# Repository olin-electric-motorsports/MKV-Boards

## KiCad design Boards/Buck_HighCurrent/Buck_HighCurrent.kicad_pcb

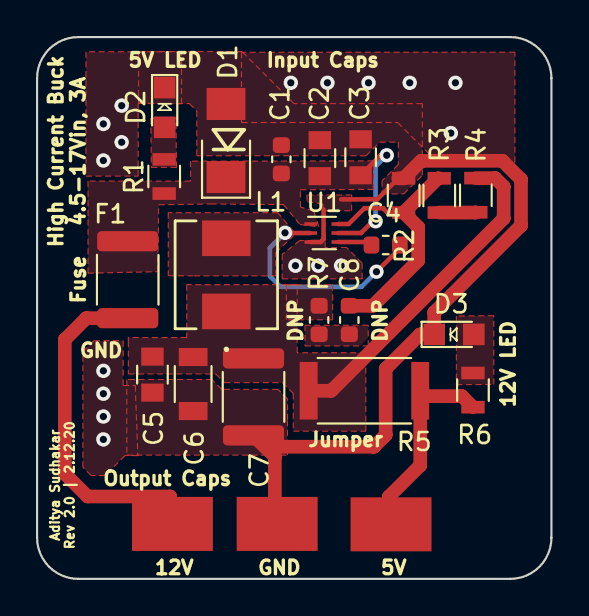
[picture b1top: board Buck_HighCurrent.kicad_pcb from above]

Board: 2 copper layers, 28.6 x 30.1 mm, 24 parts (0 on the bottom side), 12 nets.

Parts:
C1: C_0.1uF; C_0603_1608Metric
C2, C3: C_10uF_25V; C_0805_OEM
C4: C_0.1uF_0603; C_0603_1608Metric
C5: C_10uF; C_0805_OEM
C6: C_22uF; C_1206_OEM
C7: C_33uF; C_1812_4532Metric
C8: C_100nF_DNP; C_0603_1608Metric
D1: D_Zener_18V; DO-214AA
D2, D3: LED_0805; LED_0805_OEM
F1: F_2.6A_16V; Fuse_1812_4532Metric
L1: L_4.7uH_3.2A; IHLP2020BZER4R7M11
R1: R_1K; R_0805_OEM
R2: R_10K; R_0805_OEM
R3: R_51.1K; R_0805_OEM
R4: R_22K; R_0805_OEM
R5: R_0_2512; R_2512_OEM
R6: R_200; R_0805_OEM
R7: R_1_DNP; R_0603_1608Metric
TP1, TP2, TP3: Test_Point_SMD
U1: TPS563231; SOT-563

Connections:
/12V: F1.2, TP1.1
GND: C1.2, C2.2, C3.2, C5.2, C6.2, C7.2, D1.2, D2.1, D3.1, R2.2, TP3.1, U1.3
unnamed: C1.1, C2.1, C3.1, D1.1, F1.1, R1.1, U1.1, U1.5
unnamed: C4.1, L1.2, U1.2
unnamed: C4.2, U1.4
unnamed: C5.1, C6.1, C7.1, L1.1, R4.1, R5.2, R7.2
unnamed: C8.1, R2.1, R3.2, U1.6
unnamed: C8.2, R7.1
unnamed: D2.2, R1.2
unnamed: D3.2, R6.2
unnamed: R3.1, R4.2
VCC: R5.1, R6.1, TP2.1

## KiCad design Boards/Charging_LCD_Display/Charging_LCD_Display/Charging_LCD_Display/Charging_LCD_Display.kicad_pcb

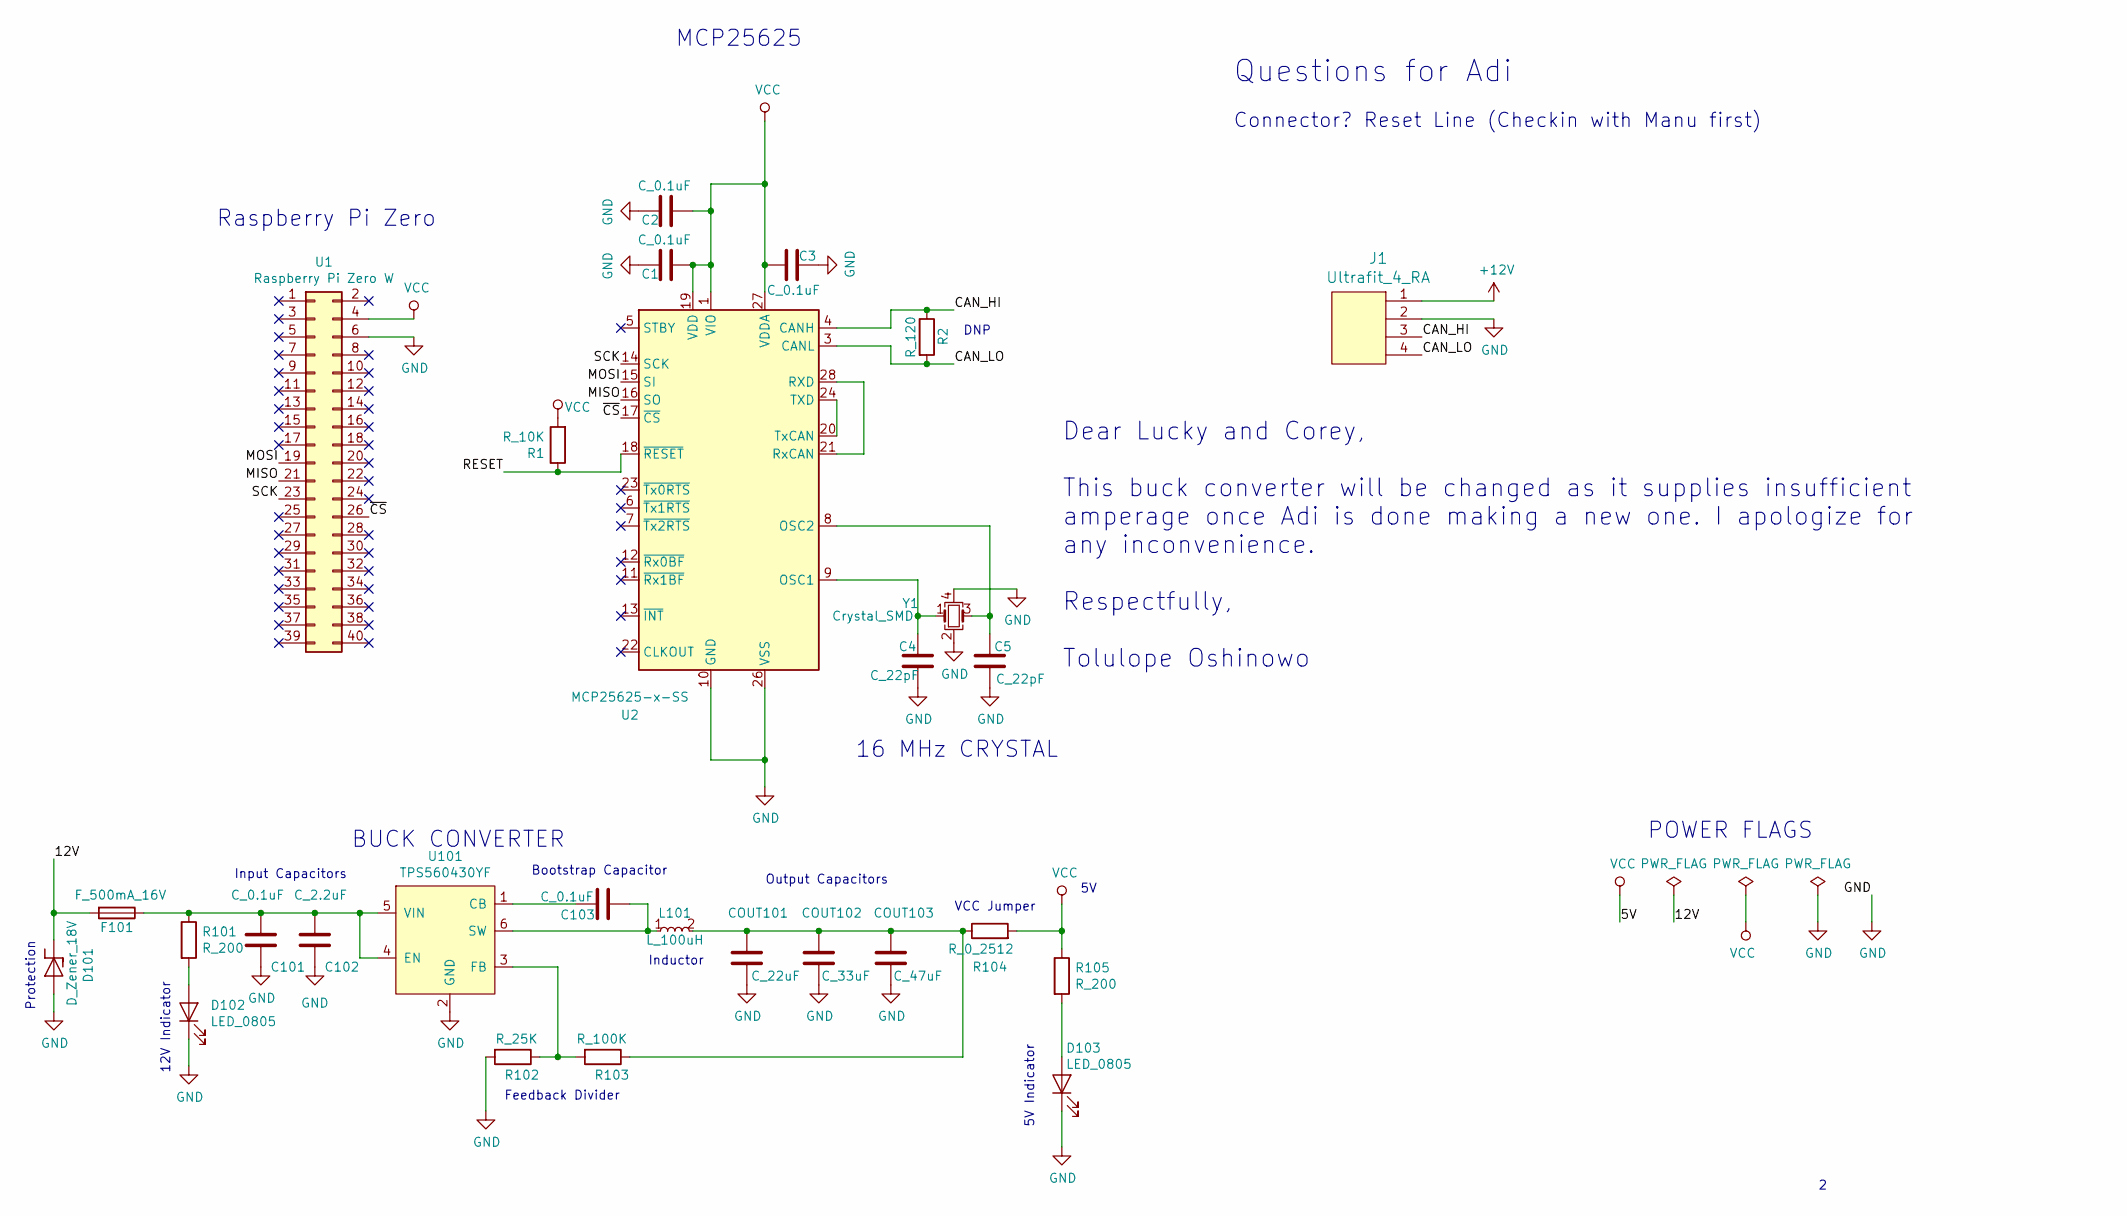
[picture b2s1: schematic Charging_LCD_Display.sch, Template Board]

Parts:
C1, C2, C3, C101, C103: C_0.1uF; C_0805_OEM; MPN 478-3352-1-ND
C4, C5: C_22pF; C_0805_OEM; MPN 1276-1130-1-ND
C102: C_2.2uF; C_0603_1608Metric; MPN 311-1451-1-ND
COUT101: C_22uF; C_1206_OEM; MPN 445-11693-1-ND
COUT102: C_33uF; Fuse_1812; MPN 445-3924-1-ND
COUT103: C_47uF; C_0805_OEM; MPN 1276-6467-1-ND
D101: D_Zener_18V; DO-214AA; MPN SMBJ5355B-TPMSCT-ND
D102, D103: LED_0805; LED_0805_OEM; MPN 475-1410-1-ND
F101: F_500mA_16V; Fuse_1210; MPN 507-1786-1-ND
J1: Ultrafit_4_RA; MPN WM11574-ND
L101: L_100uH; MPN 445-15759-1-ND
R1: R_10K; R_0805_OEM; MPN CRS0805-FX-1002ELFCT-ND
R2: R_120; R_0805_OEM; MPN RMCF0805JT200RCT-ND
R101, R105: R_200; R_0805_OEM; MPN RMCF0805JT200RCT-ND
R102: R_25K; R_0805_OEM; Digi-key Part Number CPF-A-0805B25KE
R103: R_100K; R_0805_OEM; MPN P100KCCT-ND
R104: R_0_2512; R_2512_OEM; MPN A121322CT-ND
U1: Raspberry Pi Zero W
U2: MCP25625-x-SS; SSOP-28_5.3x10.2mm_P0.65mm; MPN MCP25625-E/SS-ND
U101: TPS560430YF; SOT-23-6_OEM; MPN TPS560430YFDBVR
Y1: Crystal_SMD; Crystal_SMD_FA238; MPN 887-1125-1-ND

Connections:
+12V: J1.1
/12V: D101.1 (K), F101.2
/CAN_HI: J1.3, R2.1, U2.4 (CANH)
/CAN_LO: J1.4, R2.2, U2.3 (CANL)
/MISO: U1.21, U2.16 (SO)
/MOSI: U1.19, U2.15 (SI)
/RESET: R1.1, U2.18 (~RESET)
/SCK: U1.23, U2.14 (SCK)
/~CS: U1.26, U2.17 (~CS)
GND: C1.2, C2.2, C3.2, C4.2, C5.2, C101.2, C102.2, COUT101.2, COUT102.2, COUT103.2, D101.2 (A), D102.1 (K), D103.1 (K), J1.2, R102.2, U1.6, U2.10 (GND), U2.26 (VSS), U101.2 (GND), Y1.2, Y1.4
unnamed: C4.1, U2.9 (OSC1), Y1.1
unnamed: C5.1, U2.8 (OSC2), Y1.3
unnamed: C101.1, C102.1, F101.1, R101.1, U101.4 (EN), U101.5 (VIN)
unnamed: C103.1, U101.1 (CB)
unnamed: C103.2, L101.1, U101.6 (SW)
unnamed: COUT101.1, COUT102.1, COUT103.1, L101.2, R103.1, R104.1
unnamed: D102.2 (A), R101.2
unnamed: D103.2 (A), R105.2
unnamed: R102.1, R103.2, U101.3 (FB)
unnamed: U2.20 (TxCAN), U2.24 (TXD)
unnamed: U2.21 (RxCAN), U2.28 (RXD)
VCC: C1.1, C2.1, C3.1, R1.2, R104.2, R105.1, U1.4, U2.1 (VIO), U2.19 (VDD), U2.27 (VDDA)

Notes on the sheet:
12V Indicator
Protection
Feedback Divider
Inductor
Bootstrap Capacitor
Output Capacitors
VCC Jumper
5V Indicator
POWER FLAGS
16 MHz CRYSTAL
BUCK CONVERTER
Input Capacitors
DNP
MCP25625
Raspberry Pi Zero
Questions for Adi
Connector? Reset Line (Checkin with Manu first)
Dear Lucky and Corey, This buck converter will be changed as it supplies insufficient amperage once Adi is done making a new one. I apologize for any inconvenience. Respectfully, Tolulope Oshinowo

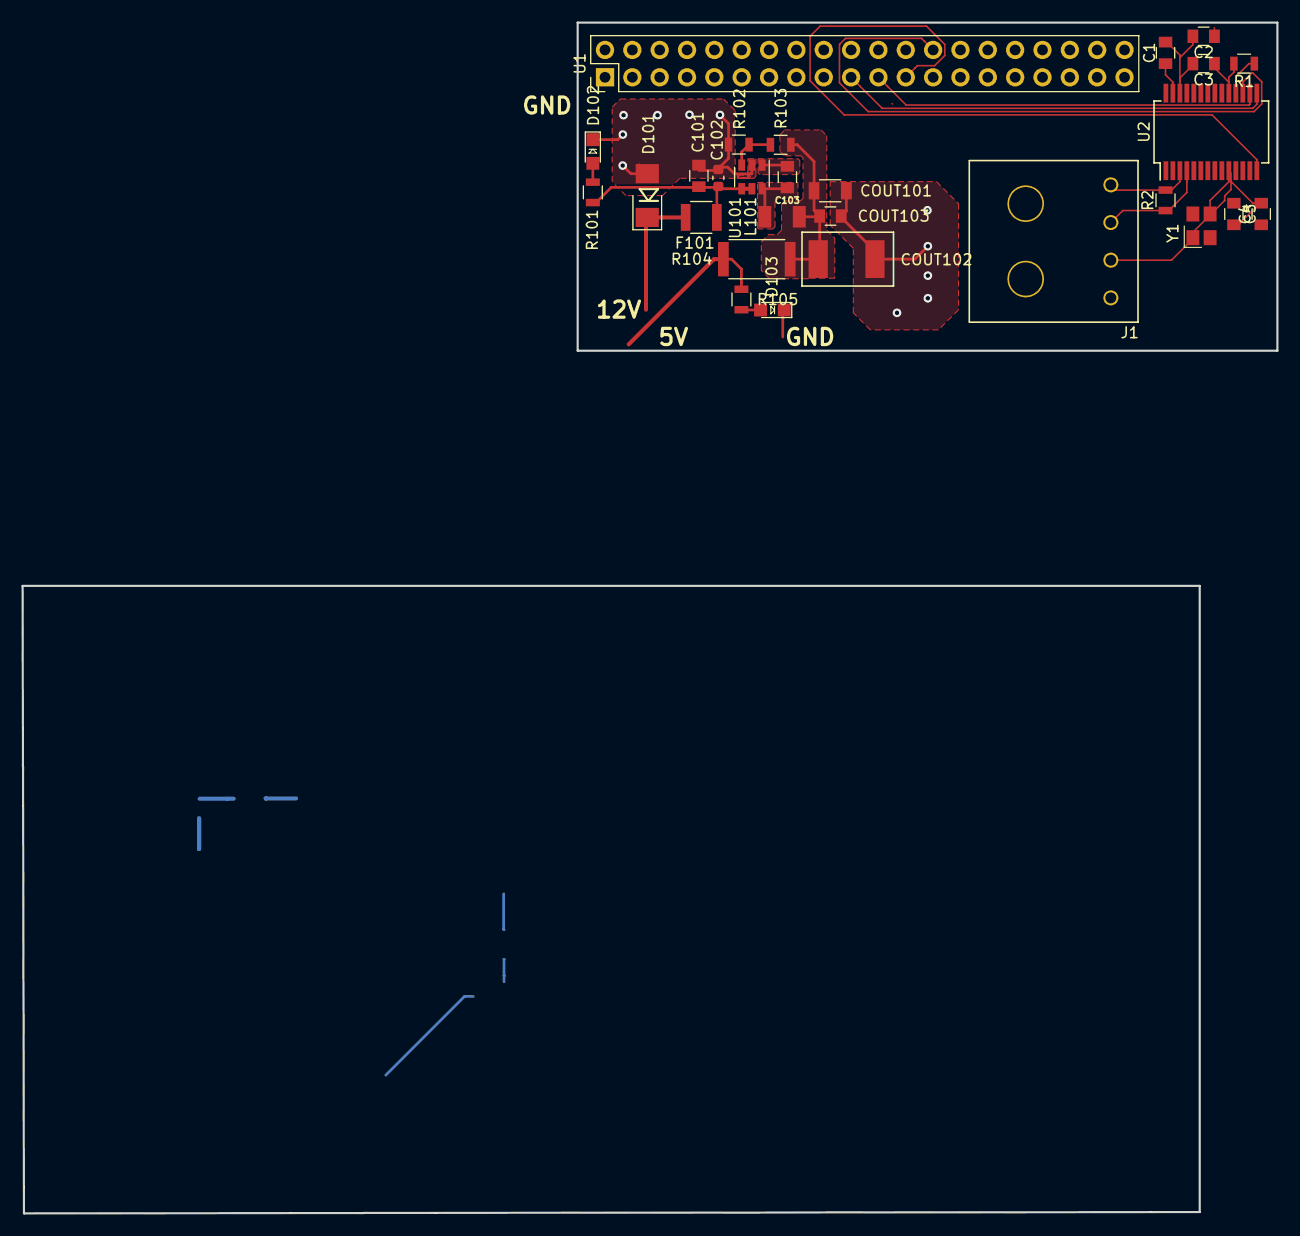
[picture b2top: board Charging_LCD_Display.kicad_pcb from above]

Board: 2 copper layers, 65.0 x 30.5 mm, 28 parts (0 on the bottom side), 21 nets.

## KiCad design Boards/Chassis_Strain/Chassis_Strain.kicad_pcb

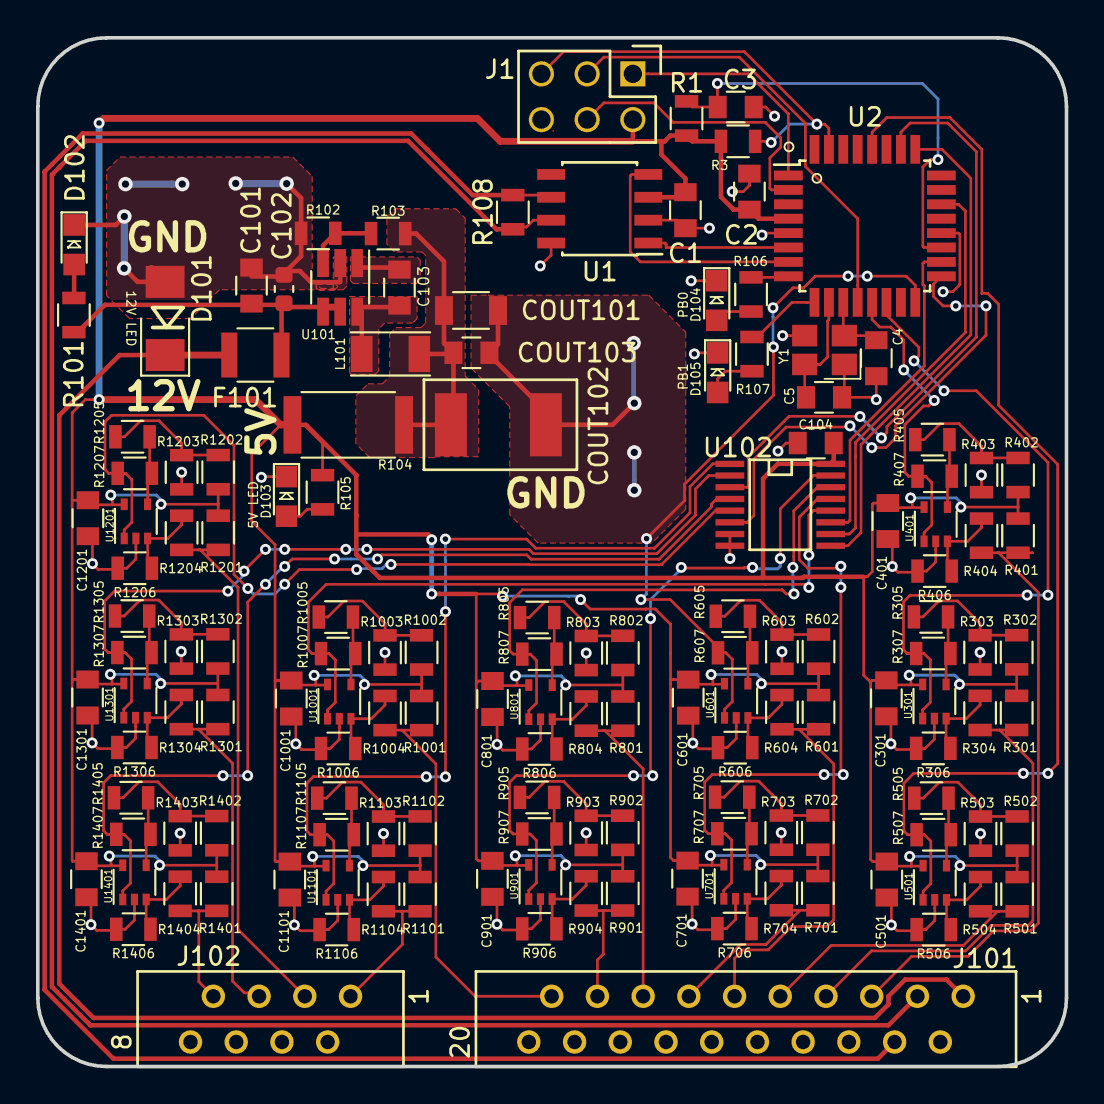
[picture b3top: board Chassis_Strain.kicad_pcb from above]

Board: 2 copper layers, 57.2 x 57.2 mm, 145 parts (0 on the bottom side), 90 nets.

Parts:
C1, C2, C101, C103, C104, C301, C401, C501, C601, C701, C801, C901, C1001, C1101, C1201, C1301, C1401: C_0.1uF; C_0805_OEM
C3: C_100pF; C_0805_OEM
C4, C5: C_30pF; C_0805_OEM
C102: C_2.2uF; C_0603_1608Metric
COUT101: C_22uF; C_1206_OEM
COUT102: C_33uF; Fuse_1812
COUT103: C_47uF; C_0805_OEM
D101: D_Zener_18V; DO-214AA
D102, D103, D104, D105: LED_0805; LED_0805_OEM
F101: F_500mA_16V; Fuse_1210
J1: CONN_02X03; Pin_Header_Straight_2x03
J101: MM_F_RA_20; micromatch_female_ra_20
J102: MM_F_RA_08; micromatch_female_ra_8
L101: L_100uH; L_100uH_OEM
R1: R_100; R_0805_OEM
R3: R_10K; R_0805_OEM
R101: R_1K; R_0805_OEM
R102: R_25K; R_0805_OEM
R103: R_100K; R_0805_OEM
R104: R_0_2512; R_2512_OEM
R105, R106, R107: R_200; R_0805_OEM
R108: R_120_DNP; R_0805_OEM
R301, R302, R303, R304, R305, R401, R402, R403, R404, R405, R501, R502, R503, R504, R505, R601, R602, R603, R604, R605, R701, R702, R703, R704, R705, R801, R802, R803, R804, R805, R901, R902, R903, R904, R905, R1001, R1002, R1003, R1004, R1005, R1101, R1102, R1103, R1104, R1105, R1201, R1202, R1203, R1204, R1205, R1301, R1302, R1303, R1304, R1305, R1401, R1402, R1403, R1404, R1405: R_120; R_0805_OEM
R306, R307, R406, R407, R506, R507, R606, R607, R706, R707, R806, R807, R906, R907, R1006, R1007, R1106, R1107, R1206, R1207, R1306, R1307, R1406, R1407: R_4.99K; R_0805_OEM
U1: MCP2561-E_SN; SOIC-8_3.9x4.9mm_Pitch1.27mm_OEM
U2: ATMEGA16M1; TQFP-32_7x7mm_Pitch0.8mm
U101: TPS560430YF; SOT-23-6_Handsoldering
U102: 74HC4051; TSSOP-16-OEM
U301, U401, U501, U601, U701, U801, U901, U1001, U1101, U1201, U1301, U1401: MCP6001T-I-LT; SOT-353_SC-70-5
Y1: Crystal_SMD; Crystal_SMD_FA238

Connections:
/12V: D101.1, F101.2, J101.1
/CAN_+: J101.3, R108.1, U1.7
/CAN_-: J101.4, R108.2, U1.6
/CAN_RX: U1.4, U2.7
/CAN_TX: U1.1, U2.6
/MISO: J1.1, U2.1
/MOSI: J1.4, U2.2
/RESET: J1.5, R3.2, U2.31
/SCK: J1.3, U2.12
/mux_enable_input: U2.17, U102.6
/mux_out_to_atmega_adc_6: U2.26, U102.3
/mux_select_S0: U2.18, U102.11
/mux_select_S1: U2.22, U102.10
/mux_select_S2: U2.25, U102.9
/sg_to_atmega_adc_2: R407.1, U2.13, U401.1
/sg_to_atmega_adc_3: R307.1, U2.14, U301.1
/sg_to_atmega_adc_4: R507.1, U2.28, U501.1
/sg_to_atmega_adc_5: R607.1, U2.16, U601.1
/sg_to_mux_Y0: R707.1, U102.13, U701.1
/sg_to_mux_Y1: R807.1, U102.14, U801.1
/sg_to_mux_Y2: R907.1, U102.15, U901.1
/sg_to_mux_Y3: R1007.1, U102.12, U1001.1
/sg_to_mux_Y4: R1107.1, U102.1, U1101.1
/sg_to_mux_Y5: R1207.1, U102.5, U1201.1
/sg_to_mux_Y6: R1307.1, U102.2, U1301.1
/sg_to_mux_Y7: R1407.1, U102.4, U1401.1
/strain_gauge_cluster/r_strain_1_+: J101.5, R401.1, R404.2
/strain_gauge_cluster/r_strain_2_+: J101.7, R301.1, R304.2
/strain_gauge_cluster/r_strain_3_+: J101.9, R501.1, R504.2
/strain_gauge_cluster/r_strain_4_+: J101.11, R601.1, R604.2
/strain_gauge_cluster/r_strain_5_+: J101.13, R701.1, R704.2
/strain_gauge_cluster/r_strain_6_+: J101.15, R801.1, R804.2
/strain_gauge_cluster/r_strain_7_+: J101.17, R901.1, R904.2
/strain_gauge_cluster/r_strain_8_+: J101.19, R1001.1, R1004.2
/strain_gauge_cluster/r_strain_9_+: J102.1, R1101.1, R1104.2
/strain_gauge_cluster/r_strain_10_+: J102.3, R1201.1, R1204.2
/strain_gauge_cluster/r_strain_11_+: J102.5, R1301.1, R1304.2
/strain_gauge_cluster/r_strain_12_+: J102.7, R1401.1, R1404.2
GND: C1.2, C2.2, C3.2, C4.2, C5.2, C101.2, C102.2, C104.2, C301.2, C401.2, C501.2, C601.2, C701.2, C801.2, C901.2, C1001.2, C1101.2, C1201.2, C1301.2, C1401.2, COUT101.2, COUT102.2, COUT103.2, D101.2, D102.1, D103.1, D104.1, D105.1, J1.6, J101.2, J101.6, J101.8, J101.10, J101.12, J101.14, J101.16, J101.18, J101.20, J102.2, J102.4, J102.6, J102.8, R102.2, R303.1, R306.2, R403.1, R406.2, R503.1, R506.2, R603.1, R606.2, R703.1, R706.2, R803.1, R806.2, R903.1, R906.2, R1003.1, R1006.2, R1103.1, R1106.2, R1203.1, R1206.2, R1303.1, R1306.2, R1403.1, R1406.2, U1.2, U1.8, U2.5, U2.20, U101.2, U102.7, U102.8, U301.2, U401.2, U501.2, U601.2, U701.2, U801.2, U901.2, U1001.2, U1101.2, U1201.2, U1301.2, U1401.2, Y1.2, Y1.4
unnamed: C3.1, R1.2, U2.19
unnamed: C4.1, U2.11, Y1.1
unnamed: C5.1, U2.10, Y1.3
unnamed: C101.1, C102.1, F101.1, R101.1, U101.4, U101.5
unnamed: C103.1, U101.1
unnamed: C103.2, L101.1, U101.6
unnamed: COUT101.1, COUT102.1, COUT103.1, L101.2, R103.1, R104.1
unnamed: D102.2, R101.2
unnamed: D103.2, R105.2
unnamed: D104.2, R106.1
unnamed: D105.2, R107.1
unnamed: R102.1, R103.2, U101.3
unnamed: R106.2, U2.8
unnamed: R107.2, U2.9
unnamed: R302.1, R303.2, R305.2
unnamed: R304.1, R306.1, U301.3
unnamed: R305.1, R307.2, U301.4
unnamed: R402.1, R403.2, R405.2
unnamed: R404.1, R406.1, U401.3
unnamed: R405.1, R407.2, U401.4
unnamed: R502.1, R503.2, R505.2
unnamed: R504.1, R506.1, U501.3
unnamed: R505.1, R507.2, U501.4
unnamed: R602.1, R603.2, R605.2
unnamed: R604.1, R606.1, U601.3
unnamed: R605.1, R607.2, U601.4
unnamed: R702.1, R703.2, R705.2
unnamed: R704.1, R706.1, U701.3
unnamed: R705.1, R707.2, U701.4
unnamed: R802.1, R803.2, R805.2
unnamed: R804.1, R806.1, U801.3
unnamed: R805.1, R807.2, U801.4
unnamed: R902.1, R903.2, R905.2
unnamed: R904.1, R906.1, U901.3
unnamed: R905.1, R907.2, U901.4
unnamed: R1002.1, R1003.2, R1005.2
unnamed: R1004.1, R1006.1, U1001.3
unnamed: R1005.1, R1007.2, U1001.4
unnamed: R1102.1, R1103.2, R1105.2
unnamed: R1104.1, R1106.1, U1101.3
unnamed: R1105.1, R1107.2, U1101.4
unnamed: R1202.1, R1203.2, R1205.2
unnamed: R1204.1, R1206.1, U1201.3
unnamed: R1205.1, R1207.2, U1201.4
unnamed: R1302.1, R1303.2, R1305.2
unnamed: R1304.1, R1306.1, U1301.3
unnamed: R1305.1, R1307.2, U1301.4
unnamed: R1402.1, R1403.2, R1405.2
unnamed: R1404.1, R1406.1, U1401.3
unnamed: R1405.1, R1407.2, U1401.4
VCC: C1.1, C2.1, C104.1, C301.1, C401.1, C501.1, C601.1, C701.1, C801.1, C901.1, C1001.1, C1101.1, C1201.1, C1301.1, C1401.1, J1.2, R1.1, R3.1, R104.2, R105.1, R301.2, R302.2, R401.2, R402.2, R501.2, R502.2, R601.2, R602.2, R701.2, R702.2, R801.2, R802.2, R901.2, R902.2, R1001.2, R1002.2, R1101.2, R1102.2, R1201.2, R1202.2, R1301.2, R1302.2, R1401.2, R1402.2, U1.3, U2.4, U102.16, U301.5, U401.5, U501.5, U601.5, U701.5, U801.5, U901.5, U1001.5, U1101.5, U1201.5, U1301.5, U1401.5

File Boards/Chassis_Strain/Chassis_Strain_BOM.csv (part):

Reference, Value, Footprint, Datasheet, MFN, MPN, PurchasingLink, Digi-key Part Number, Link, Purchasing Link
"C102","C_2.2uF","footprints:C_0603_1608Metric","http://www.yageo.com/documents/recent/UPY-GPHC_X5R_4V-to-50V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","DK","311-1451-1-ND","https://www.digikey.com/product-detail/en/yageo/CC0603KRX5R6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","","",""
"C101","C_0.1uF","footprints:C_0805_OEM","http://datasheets.avx.com/X7RDielectric.pdf","DK","478-3352-1-ND","https://www.digikey.com/products/en?keywords=478-3352-1-ND","","",""
"R103","R_100K","footprints:R_0805_OEM","https://industrial.panasonic.com/cdbs/www-data/pdf/RDA0000/A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","DK","P100KCCT-ND","https://www.digikey.com/product-detail/en/panasonic-electron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","","",""
"C103","C_0.1uF","footprints:C_0805_OEM","http://datasheets.avx.com/X7RDielectric.pdf","DK","478-3352-1-ND","https://www.digikey.com/products/en?keywords=478-3352-1-ND","","",""
"COUT101","C_22uF","footprints:C_1206_OEM","https://product.tdk.com/info/en/catalog/datasheets/mlcc_comm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","DK","445-11693-1-ND","https://www.digikey.com/product-detail/en/tdk-corporation/C3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","","",""
"COUT103","C_47uF","footprints:C_0805_OEM","http://www.samsungsem.com/kr/support/product-search/mlcc/__i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","DK","1276-6467-1-ND","https://www.digikey.com/product-detail/en/samsung-electro-me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","","",""
"COUT102","C_33uF","footprints:C_1812_OEM","https://product.tdk.com/info/en/catalog/datasheets/mlcc_comm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","C4532X7R1C336M250KC","445-3924-1-ND","https://www.digikey.com/product-detail/en/tdk-corporation/C4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","","",""
"R102","R_25K","footprints:R_0805_OEM","https://www.te.com/commerce/DocumentDelivery/DDEController?A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","A124124CT-ND","","https://www.digikey.com/product-detail/en/te-connectivity-pa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","CPF-A-0805B25KE","",""
"F101","F_500mA_16V","footprints:Fuse_1210","https://belfuse.com/resources/CircuitProtection/datasheets/0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","DK","507-1786-1-ND","https://www.digikey.com/product-detail/en/bel-fuse-inc/0ZCH0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","","",""
"R104","R_0_2512","footprints:R_2512_OEM","http://www.te.com/commerce/DocumentDelivery/DDEController?Ac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","DK","A121322CT-ND","https://www.digikey.com/products/en?keywords=A121322CT-ND","","",""
"D103","LED_0805","footprints:LED_0805_OEM","http://www.osram-os.com/Graphics/XPic9/00078860_0.pdf","DK","475-1410-1-ND","https://www.digikey.com/products/en?keywords=475-1410-1-ND","","",""
"R105","R_200","footprints:R_0805_OEM","https://www.seielect.com/Catalog/SEI-RMCF_RMCP.pdf","DK","RMCF0805JT200RCT-ND","https://www.digikey.com/products/en?keywords=RMCF0805JT200RCT-ND","","",""
"D101","D_Zener_18V","footprints:DO-214AA","http://www.mccsemi.com/up_pdf/SMBJ5338B-SMBJ5388B(SMB).pdf","DK","SMBJ5355B-TPMSCT-ND","https://www.digikey.com/products/en?keywords=SMBJ5355B-TPMSCT-ND","","",""
"D102","LED_0805","footprints:LED_0805_OEM","http://www.osram-os.com/Graphics/XPic9/00078860_0.pdf","DK","475-1410-1-ND","https://www.digikey.com/products/en?keywords=475-1410-1-ND","","",""
"L101","L_100uH","footprints:L_100uH_OEM","https://product.tdk.com/info/en/catalog/datasheets/inductor_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","Digikey","445-15759-1-ND","","","https://www.digikey.com/product-detail/en/tdk-corporation/NL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",""
"R1","R_100","footprints:R_0805_OEM","https://www.seielect.com/Catalog/SEI-rncp.pdf","DK","RNCP0805FTD100RCT-ND","https://www.digikey.com/products/en?keywords=RNCP0805FTD100RCT-ND","","",""
"C3","C_100pF","footprints:C_0805_OEM","https://katalog.we-online.de/pbs/datasheet/885012007057.pdf","DK","732-7852-1-ND","https://www.digikey.com/product-detail/en/wurth-electronics-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","","",""
"Y1","Crystal_SMD","footprints:Crystal_SMD_FA238","http://www.txccorp.com/download/products/quartz_crystals/201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","DK","887-1125-1-ND","https://www.digikey.com/product-detail/en/txc-corporation/7M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","","",""
"C4","C_30pF","footprints:C_0805_OEM","https://media.digikey.com/pdf/Data%20Sheets/Samsung%20PDFs/C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","DK","1276-1130-1-ND","https://www.digikey.com/product-detail/en/samsung-electro-me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","","",""
"C5","C_30pF","footprints:C_0805_OEM","https://media.digikey.com/pdf/Data%20Sheets/Samsung%20PDFs/C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","DK","1276-1130-1-ND","https://www.digikey.com/product-detail/en/samsung-electro-me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","","",""
"R3","R_10K","footprints:R_0805_OEM","http://www.bourns.com/data/global/pdfs/CRS.pdf","DK","CRS0805-FX-1002ELFCT-ND","https://www.digikey.com/products/en?keywords=CRS0805-FX-1002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","","",""
"U1","MCP2561-E_SN","footprints:SOIC-8_3.9x4.9mm_Pitch1.27mm_OEM","http://www.microchip.com/mymicrochip/filehandler.aspx?ddocna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","DK","MCP2561-E/SN-ND","https://www.digikey.com/products/en?keywords=mcp2561-e%2Fsn","","",""
"C1","C_0.1uF","footprints:C_0805_OEM","http://datasheets.avx.com/X7RDielectric.pdf","DK","478-3352-1-ND","https://www.digikey.com/products/en?keywords=478-3352-1-ND","","",""
"J1","CONN_02X03","footprints:Pin_Header_Straight_2x03","http://portal.fciconnect.com/Comergent//fci/drawing/67996.pdf","DK","609-3234-ND","https://www.digikey.com/product-detail/en/amphenol-fci/67997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","","",""
"C2","C_0.1uF","footprints:C_0805_OEM","http://datasheets.avx.com/X7RDielectric.pdf","DK","478-3352-1-ND","https://www.digikey.com/products/en?keywords=478-3352-1-ND","","",""
"U101","TPS560430YF","Package_TO_SOT_SMD:SOT-23-6_Handsoldering","http://www.ti.com/lit/ds/symlink/tps560430.pdf","TPS560430YFDBVR-ND","TPS560430YFDBVR","","","","https://www.digikey.com/product-detail/en/texas-instruments/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"
"U2","ATMEGA16M1","footprints:TQFP-32_7x7mm_Pitch0.8mm","http://ww1.microchip.com/downloads/en/DeviceDoc/Atmel-8209-8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","DK","ATMEGA16M1-AU-ND","https://www.digikey.com/product-detail/en/atmel/ATMEGA16M1-A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","","",""
"J101","MM_F_RA_20","footprints:micromatch_female_ra_20","http://www.te.com/commerce/DocumentDelivery/DDEController?Ac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","TE","2-338070-0","http://www.te.com/usa-en/product-2-338070-0.html","","",""
"J102","MM_F_RA_08","footprints:micromatch_female_ra_8","http://www.te.com/commerce/DocumentDelivery/DDEController?Ac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","TE","338070-8","http://www.te.com/usa-en/product-338070-8.html","","",""
"R108","R_120_DNP","footprints:R_0805_OEM","https://www.mouser.com/datasheet/2/315/AOA0000C304-1149620.pdf","DK","667-ERJ-6ENF1200V","https://www.mouser.com/ProductDetail/Panasonic-Industrial-De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","","",""
"U102","74HC4051","footprints:TSSOP-16-OEM","https://assets.nexperia.com/documents/data-sheet/74HC_HCT405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","DK","1727-1033-1-ND","https://www.digikey.com/product-detail/en/nexperia-usa-inc/7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","","",""
"R101","R_1K","footprints:R_0805_OEM","https://www.seielect.com/Catalog/SEI-rncp.pdf","DK","RNCP0805FTD1K00CT-ND","https://www.digikey.com/products/en?keywords=RNCP0805FTD1K00CT-ND","","",""
"D104","LED_0805","footprints:LED_0805_OEM","http://www.osram-os.com/Graphics/XPic9/00078860_0.pdf","DK","475-1410-1-ND","https://www.digikey.com/products/en?keywords=475-1410-1-ND","","",""
"R106","R_200","footprints:R_0805_OEM","https://www.seielect.com/Catalog/SEI-RMCF_RMCP.pdf","DK","RMCF0805JT200RCT-ND","https://www.digikey.com/products/en?keywords=RMCF0805JT200RCT-ND","","",""
"D105","LED_0805","footprints:LED_0805_OEM","http://www.osram-os.com/Graphics/XPic9/00078860_0.pdf","DK","475-1410-1-ND","https://www.digikey.com/products/en?keywords=475-1410-1-ND","","",""
"R107","R_200","footprints:R_0805_OEM","https://www.seielect.com/Catalog/SEI-RMCF_RMCP.pdf","DK","RMCF0805JT200RCT-ND","https://www.digikey.com/products/en?keywords=RMCF0805JT200RCT-ND","","",""
"C104","C_0.1uF","footprints:C_0805_OEM","http://datasheets.avx.com/X7RDielectric.pdf","DK","478-3352-1-ND","https://www.digikey.com/products/en?keywords=478-3352-1-ND","","",""
"R306","R_4.99K","footprints:R_0805_OEM","https://www.digikey.com/product-detail/en/yageo/RC0402FR-074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","DK","RNCP0805FTD4K99CT-ND ","https://www.digikey.com/product-detail/en/stackpole-electron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","","",""
"R305","R_120","footprints:R_0805_OEM","https://www.mouser.com/datasheet/2/315/AOA0000C304-1149620.pdf","DK","667-ERJ-6ENF1200V","https://www.mouser.com/ProductDetail/Panasonic-Industrial-De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","","",""
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
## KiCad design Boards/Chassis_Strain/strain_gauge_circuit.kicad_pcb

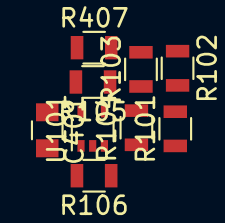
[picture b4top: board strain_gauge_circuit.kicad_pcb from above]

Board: 2 copper layers, 9 parts (0 on the bottom side), 7 nets, no tracks yet.

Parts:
C401: C_0.1uF; C_0805_OEM
R101, R102, R103, R104, R105: R_120; R_0805_OEM
R106, R407: R_4.99K; R_0805_OEM
U101: MCP6001T-I-LT; SOT-353_SC-70-5

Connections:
/r_strain_+: R101.1, R104.2
/strain_gauge_vout: R407.1, U101.1
GND: C401.2, R103.1, R106.2, U101.2
unnamed: R102.1, R103.2, R105.2
unnamed: R104.1, R106.1, U101.3
unnamed: R105.1, R407.2, U101.4
VCC: C401.1, R101.2, R102.2, U101.5

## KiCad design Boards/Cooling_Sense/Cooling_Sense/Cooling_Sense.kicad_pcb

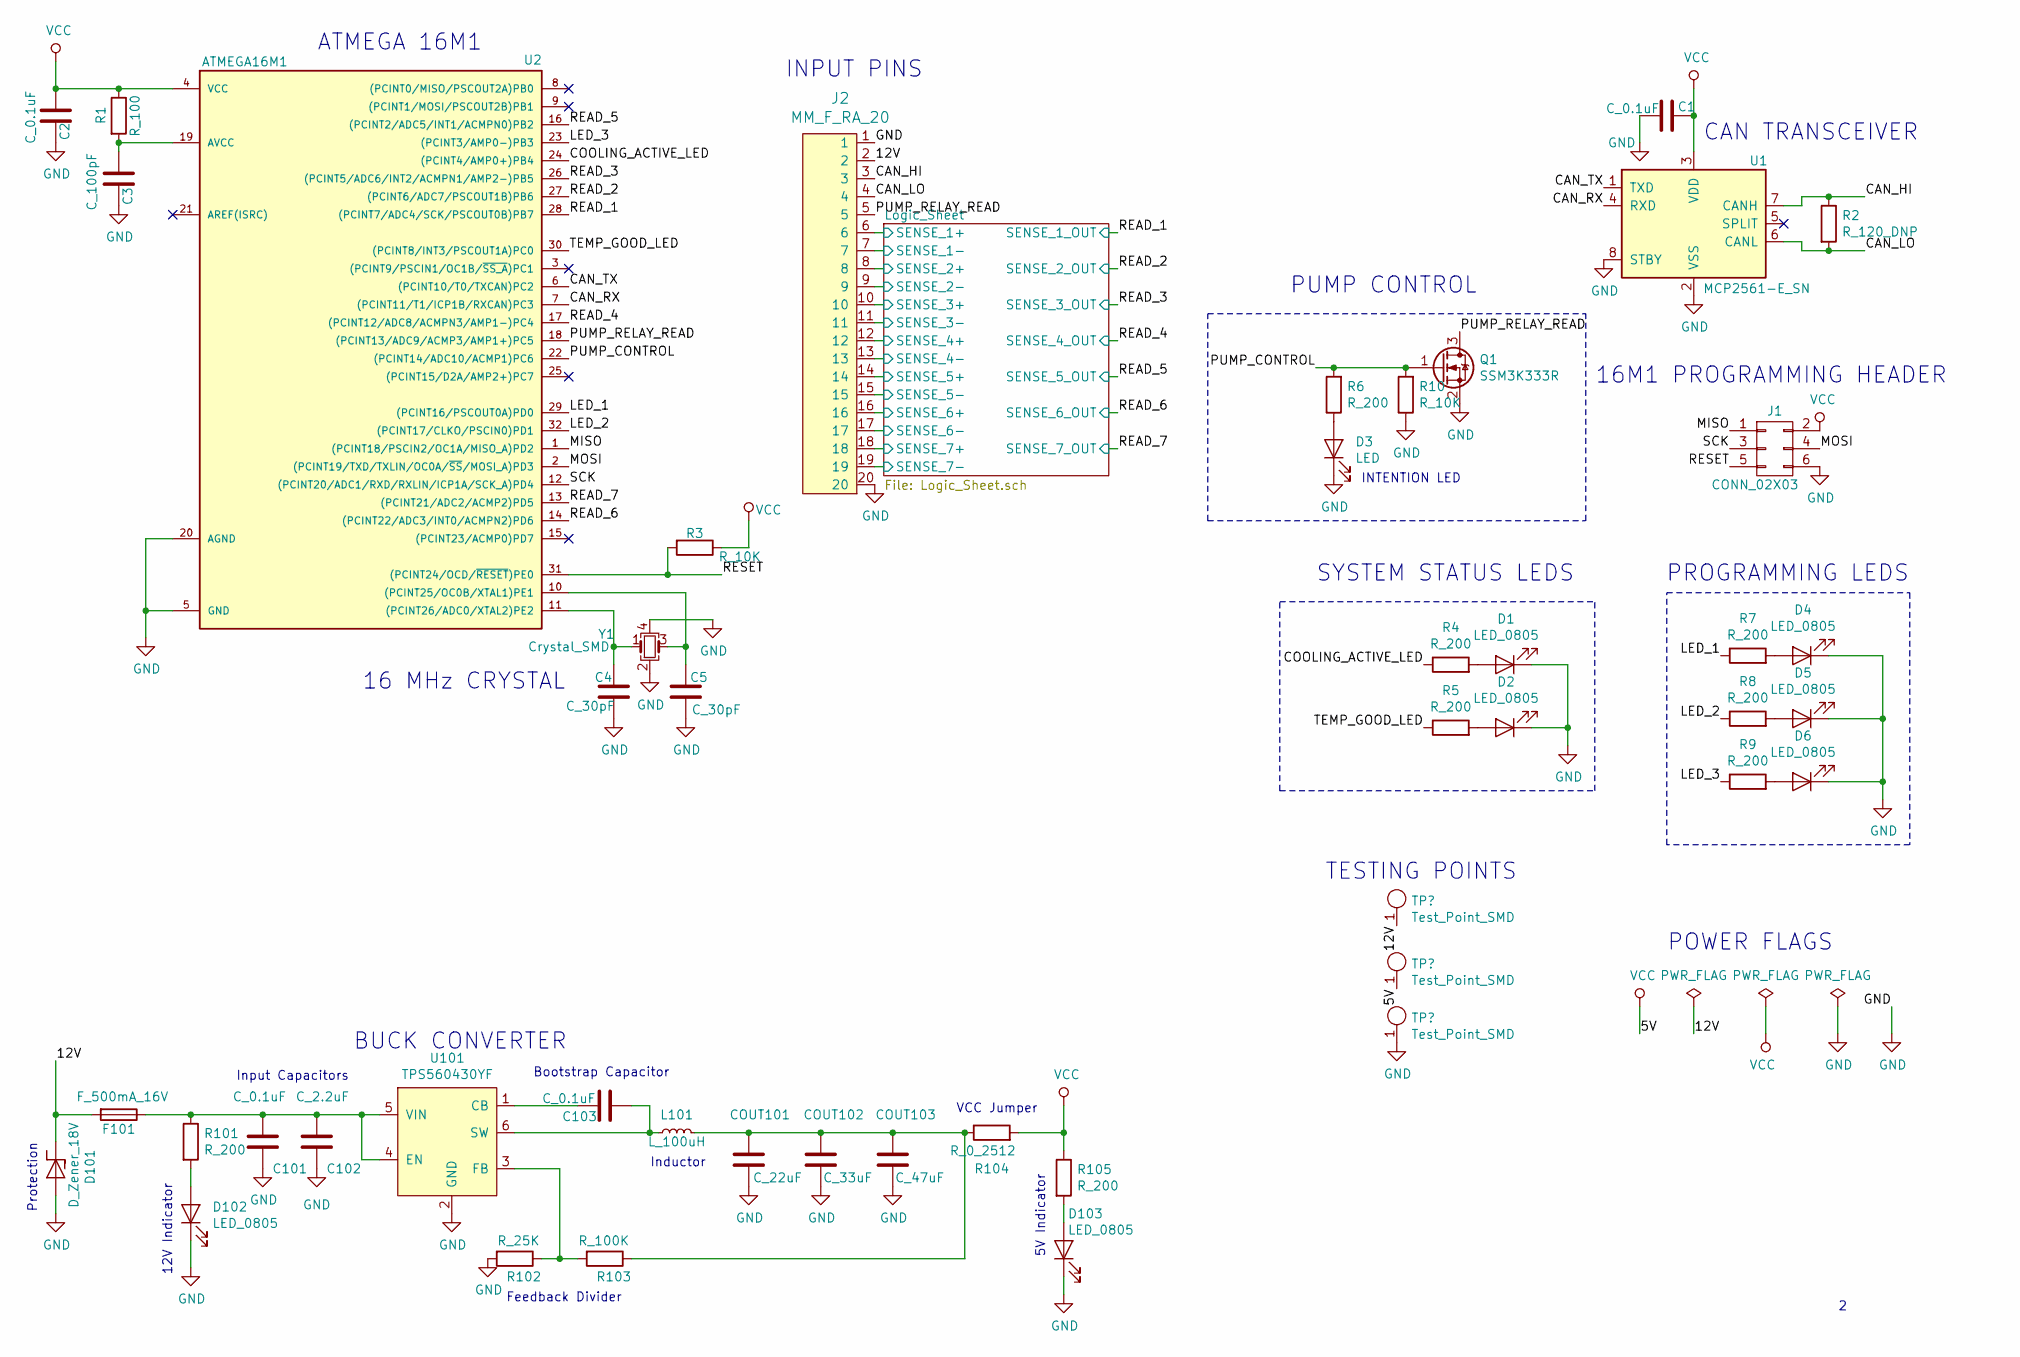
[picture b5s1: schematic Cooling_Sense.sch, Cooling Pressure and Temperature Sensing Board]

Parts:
C1, C2, C101, C103: C_0.1uF; C_0805_OEM; MPN 478-3352-1-ND
C3: C_100pF; C_0805_OEM; MPN 732-7852-1-ND
C4, C5: C_30pF; C_0805_OEM; MPN 1276-1130-1-ND
C102: C_2.2uF; C_0603_1608Metric; MPN 311-1451-1-ND
COUT101: C_22uF; C_1206_OEM; MPN 445-11693-1-ND
COUT102: C_33uF; Fuse_1812; MPN 445-3924-1-ND
COUT103: C_47uF; C_0805_OEM; MPN 1276-6467-1-ND
D1, D2, D4, D5, D6, D102, D103: LED_0805; LED_0805_OEM; MPN 475-1410-1-ND
D3: LED
D101: D_Zener_18V; DO-214AA; MPN SMBJ5355B-TPMSCT-ND
F101: F_500mA_16V; Fuse_1210; MPN 507-1786-1-ND
J1: CONN_02X03; Pin_Header_Straight_2x03; MPN 609-3234-ND
J2: MM_F_RA_20; micromatch_female_ra_20; MPN 2-338070-0
L101: L_100uH; MPN 445-15759-1-ND
Q1: SSM3K333R; SOT-23F; MPN SSM3K333RLFCT-ND
R1: R_100; R_0805_OEM; MPN RNCP0805FTD100RCT-ND
R2: R_120_DNP; R_0805_OEM; MPN 667-ERJ-6ENF1200V
R3, R10: R_10K; R_0805_OEM; MPN CRS0805-FX-1002ELFCT-ND
R4, R5, R6, R7, R8, R9, R101, R105: R_200; R_0805_OEM; MPN RMCF0805JT200RCT-ND
R102: R_25K; R_0805_OEM; Digi-key Part Number CPF-A-0805B25KE
R103: R_100K; R_0805_OEM; MPN P100KCCT-ND
R104: R_0_2512; R_2512_OEM; MPN A121322CT-ND
U1: MCP2561-E_SN; SOIC-8_3.9x4.9mm_Pitch1.27mm_OEM; MPN MCP2561-E/SN-ND
U2: ATMEGA16M1; TQFP-32_7x7mm_Pitch0.8mm; MPN ATMEGA16M1-AU-ND
U101: TPS560430YF; SOT-23-6_OEM; MPN TPS560430YFDBVR
Y1: Crystal_SMD; Crystal_SMD_FA238; MPN 887-1125-1-ND

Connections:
/12V: D101.1 (K), F101.2, J2.2; also elsewhere on the board
/CAN_HI: J2.3, R2.1, U1.7 (CANH)
/CAN_LO: J2.4, R2.2, U1.6 (CANL)
/CAN_RX: U1.4 (RXD), U2.7 ((PCINT11/T1/ICP1B/RXCAN)PC3)
/CAN_TX: U1.1 (TXD), U2.6 ((PCINT10/T0/TXCAN)PC2)
/COOLING_ACTIVE_LED: R4.1, U2.24 ((PCINT4/AMP0+)PB4)
/LED_1: R7.1, U2.29 ((PCINT16/PSCOUT0A)PD0)
/LED_2: R8.1, U2.32 ((PCINT17/CLKO/PSCIN0)PD1)
/LED_3: R9.1, U2.23 ((PCINT3/AMP0-)PB3)
/Logic_Sheet/SENSE_1+: J2.6; also elsewhere on the board
/Logic_Sheet/SENSE_1-: J2.7; also elsewhere on the board
/Logic_Sheet/SENSE_2+: J2.8; also elsewhere on the board
/Logic_Sheet/SENSE_2-: J2.9; also elsewhere on the board
/Logic_Sheet/SENSE_3+: J2.10; also elsewhere on the board
/Logic_Sheet/SENSE_3-: J2.11; also elsewhere on the board
/Logic_Sheet/SENSE_4+: J2.12; also elsewhere on the board
/Logic_Sheet/SENSE_4-: J2.13; also elsewhere on the board
/Logic_Sheet/SENSE_5+: J2.14; also elsewhere on the board
/Logic_Sheet/SENSE_5-: J2.15; also elsewhere on the board
/Logic_Sheet/SENSE_6+: J2.16; also elsewhere on the board
/Logic_Sheet/SENSE_6-: J2.17; also elsewhere on the board
/Logic_Sheet/SENSE_7+: J2.18; also elsewhere on the board
/Logic_Sheet/SENSE_7-: J2.19; also elsewhere on the board
/MISO: J1.1, U2.1 ((PCINT18/PSCIN2/OC1A/MISO_A)PD2)
/MOSI: J1.4, U2.2 ((PCINT19/TXD/TXLIN/OC0A/~SS~/MOSI_A)PD3)
/PUMP_CONTROL: Q1.1 (G), R6.2, R10.2, U2.22 ((PCINT14/ADC10/ACMP1)PC6)
/PUMP_RELAY_READ: J2.5, Q1.3 (D), U2.18 ((PCINT13/ADC9/ACMP3/AMP1+)PC5)
/READ_1: U2.28 ((PCINT7/ADC4/SCK/PSCOUT0B)PB7); also elsewhere on the board
/READ_2: U2.27 ((PCINT6/ADC7/PSCOUT1B)PB6); also elsewhere on the board
/READ_3: U2.26 ((PCINT5/ADC6/INT2/ACMPN1/AMP2-)PB5); also elsewhere on the board
/READ_4: U2.17 ((PCINT12/ADC8/ACMPN3/AMP1-)PC4); also elsewhere on the board
/READ_5: U2.16 ((PCINT2/ADC5/INT1/ACMPN0)PB2); also elsewhere on the board
/READ_6: U2.14 ((PCINT22/ADC3/INT0/ACMPN2)PD6); also elsewhere on the board
/READ_7: U2.13 ((PCINT21/ADC2/ACMP2)PD5); also elsewhere on the board
/RESET: J1.5, R3.2, U2.31 ((PCINT24/OCD/~RESET~)PE0)
/SCK: J1.3, U2.12 ((PCINT20/ADC1/RXD/RXLIN/ICP1A/SCK_A)PD4)
/TEMP_GOOD_LED: R5.1, U2.30 ((PCINT8/INT3/PSCOUT1A)PC0)
GND: C1.2, C2.2, C3.2, C4.2, C5.2, C101.2, C102.2, COUT101.2, COUT102.2, COUT103.2, D1.1 (K), D2.1 (K), D3.1 (K), D4.1 (K), D5.1 (K), D6.1 (K), D101.2 (A), D102.1 (K), D103.1 (K), J1.6, J2.1, J2.20, Q1.2 (S), R10.1, R102.2, U1.2 (VSS), U1.8 (STBY), U2.5 (GND), U2.20 (AGND), U101.2 (GND), Y1.2, Y1.4; also elsewhere on the board
unnamed: C3.1, R1.2, U2.19 (AVCC)
unnamed: C4.1, U2.11 ((PCINT26/ADC0/XTAL2)PE2), Y1.1
unnamed: C5.1, U2.10 ((PCINT25/OC0B/XTAL1)PE1), Y1.3
unnamed: C101.1, C102.1, F101.1, R101.1, U101.4 (EN), U101.5 (VIN)
unnamed: C103.1, U101.1 (CB)
unnamed: C103.2, L101.1, U101.6 (SW)
unnamed: COUT101.1, COUT102.1, COUT103.1, L101.2, R103.1, R104.1
unnamed: D1.2 (A), R4.2
unnamed: D2.2 (A), R5.2
unnamed: D3.2 (A), R6.1
unnamed: D4.2 (A), R7.2
unnamed: D5.2 (A), R8.2
unnamed: D6.2 (A), R9.2
unnamed: D102.2 (A), R101.2
unnamed: D103.2 (A), R105.2
unnamed: R102.1, R103.2, U101.3 (FB)
VCC: C1.1, C2.1, J1.2, R1.1, R3.1, R104.2, R105.1, U1.3 (VDD), U2.4 (VCC); also elsewhere on the board

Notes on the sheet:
Input Capacitors
12V Indicator
Protection
BUCK CONVERTER
Feedback Divider
Inductor
Bootstrap Capacitor
VCC Jumper
5V Indicator
CAN TRANSCEIVER
ATMEGA 16M1
16 MHz CRYSTAL
POWER FLAGS
16M1 PROGRAMMING HEADER
SYSTEM STATUS LEDS
PROGRAMMING LEDS
INPUT PINS
PUMP CONTROL
INTENTION LED
TESTING POINTS

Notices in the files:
parts and their libraries:
Copyright 2016 Accelerated Designs. All rights reserved.
